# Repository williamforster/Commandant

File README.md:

SmartVac displays GPS and other data on a map.

# Usage

Download xampp or a similar software and find the website directory (htdocs)

Remove the default xampp webpage so the htdocs directory is empty.
Navigate to htdocs and clone into the current directory.

    git clone https://github.com/williamforster/SmartVac.git .

Download and install node.
Then install the project dependencies.

    npm install

Open your web browser and type 'localhost/phpmyadmin' in the address bar. Add a new database and run the sql in create_test_datatable.sql - or at least create a table with similar columns.

Add a user account in phpmyadmin and grant them Data priveleges.

Make a credentials.php file and enter the new fields. Credentials.php is in the .gitignore file so it won't be uploaded to the git repo.

    cp credentials_example.php credentials.php
    nano credentials.php

Build bundle.js with browserify. Bundles include only the js needed by the website.

    npm run build

Open localhost in your web browser

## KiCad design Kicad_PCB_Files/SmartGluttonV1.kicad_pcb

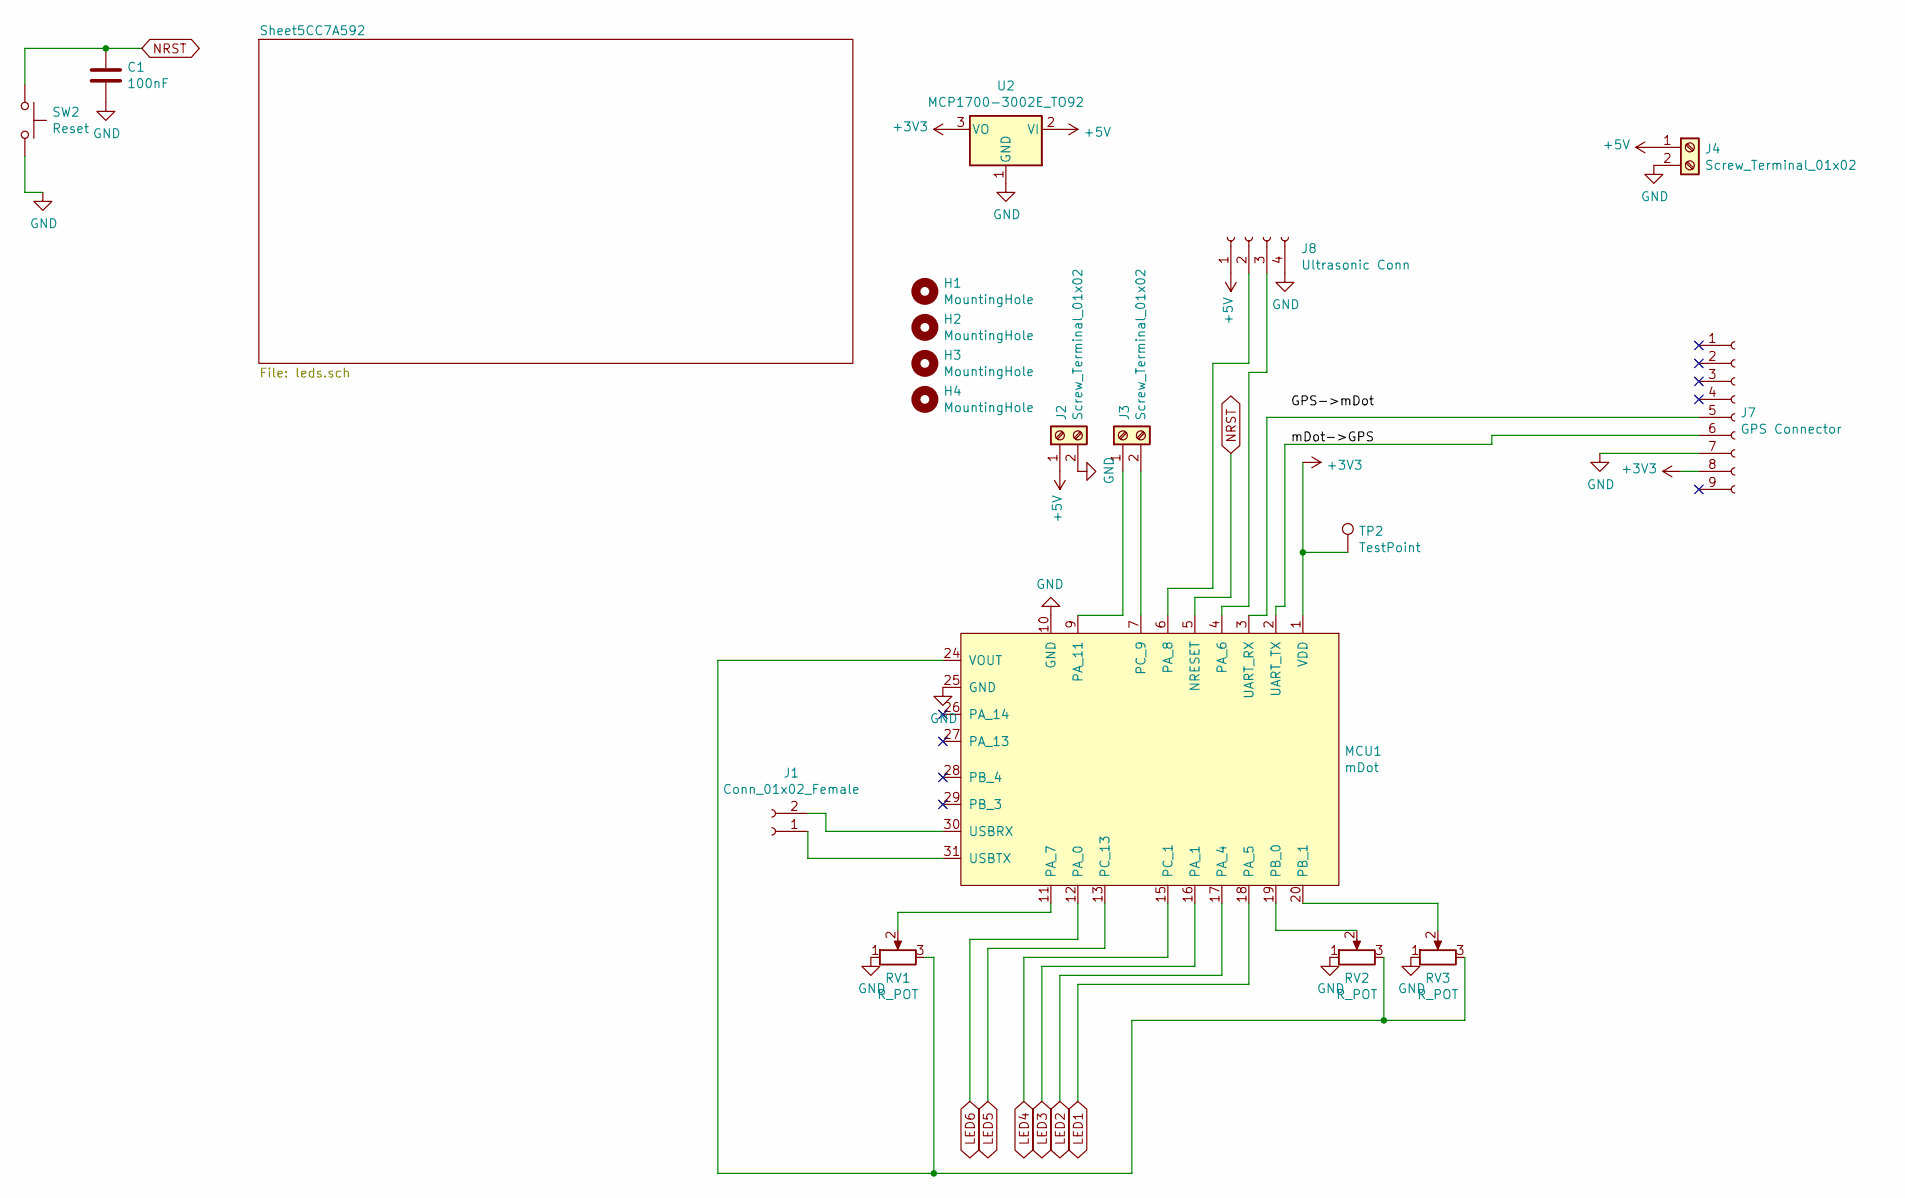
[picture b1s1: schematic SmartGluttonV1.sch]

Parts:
C1: 100nF; C_0805_2012Metric_Pad1.15x1.40mm_HandSolder
H1, H2, H3, H4: MountingHole; MountingHole_4mm
J1: Conn_01x02_Female; PinHeader_1x02_P2.54mm_Vertical
J2, J3, J4: Screw_Terminal_01x02; TerminalBlock_bornier-2_P5.08mm
J7: GPS Connector; Adafruit_GPS_Breakout
J8: Ultrasonic Conn; PinSocket_1x04_P2.54mm_Vertical
MCU1: mDot; mdot
RV1, RV2, RV3: R_POT; Potentiometer_Bourns_3296W_Vertical
SW2: Reset; SW_PUSH_6mm
TP2: TestPoint; TestPoint_Pad_3.0x3.0mm
U2: MCP1700-3002E_TO92; TO-92_HandSolder

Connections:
+3V3: J7.8, MCU1.1 (VDD), TP2.1, U2.3 (VO)
+5V: J2.1, J4.1, J8.1, U2.2 (VI); also elsewhere on the board
/mDot->GPS: J7.6, MCU1.2 (UART_TX)
GND: C1.2, J2.2, J4.2, J7.7, J8.4, MCU1.10 (GND), MCU1.25 (GND), RV1.1, RV2.1, RV3.1, SW2.2, U2.1 (GND); also elsewhere on the board
LED1: MCU1.18 (PA_5); also elsewhere on the board
LED2: MCU1.17 (PA_4); also elsewhere on the board
LED3: MCU1.16 (PA_1); also elsewhere on the board
LED4: MCU1.15 (PC_1); also elsewhere on the board
LED5: MCU1.13 (PC_13); also elsewhere on the board
LED6: MCU1.12 (PA_0); also elsewhere on the board
NRST: C1.1, MCU1.5 (NRESET), SW2.1
unnamed: J1.1, MCU1.31 (USBTX)
unnamed: J1.2, MCU1.30 (USBRX)
unnamed: J3.1, MCU1.9 (PA_11)
unnamed: J3.2, MCU1.7 (PC_9)
unnamed: J7.5, MCU1.3 (UART_RX)
unnamed: J8.2, MCU1.6 (PA_8)
unnamed: J8.3, MCU1.4 (PA_6)
unnamed: MCU1.11 (PA_7), RV1.2
unnamed: MCU1.19 (PB_0), RV2.2
unnamed: MCU1.20 (PB_1), RV3.2
unnamed: MCU1.24 (VOUT), RV1.3, RV2.3, RV3.3

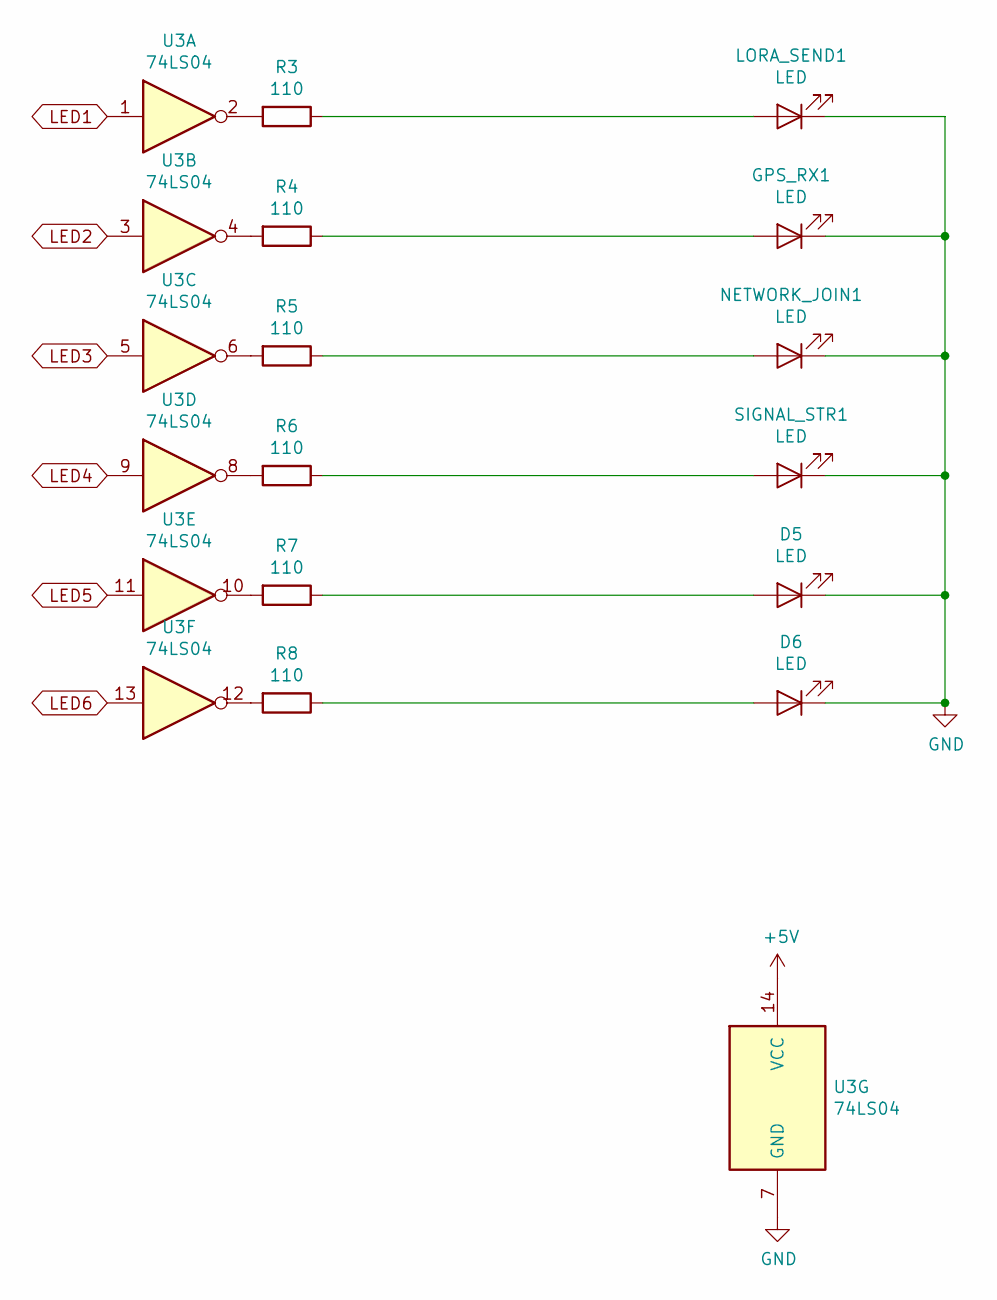
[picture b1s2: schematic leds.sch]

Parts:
D5, D6: LED; LED_D3.0mm
GPS_RX1: LED; LED_D3.0mm
LORA_SEND1: LED; LED_D3.0mm
NETWORK_JOIN1: LED; LED_D3.0mm
R3, R4, R5, R6, R7, R8: 110; R_0805_2012Metric_Pad1.15x1.40mm_HandSolder
SIGNAL_STR1: LED; LED_D3.0mm
U3: 74LS04; DIP-14_W7.62mm_LongPads

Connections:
+5V: U3.14 (VCC); also elsewhere on the board
GND: D5.1 (K), D6.1 (K), GPS_RX1.1 (K), LORA_SEND1.1 (K), NETWORK_JOIN1.1 (K), SIGNAL_STR1.1 (K), U3.7 (GND); also elsewhere on the board
LED1: U3.1; also elsewhere on the board
LED2: U3.3; also elsewhere on the board
LED3: U3.5; also elsewhere on the board
LED4: U3.9; also elsewhere on the board
LED5: U3.11; also elsewhere on the board
LED6: U3.13; also elsewhere on the board
unnamed: D5.2 (A), R7.1
unnamed: D6.2 (A), R8.1
unnamed: GPS_RX1.2 (A), R4.1
unnamed: LORA_SEND1.2 (A), R3.1
unnamed: NETWORK_JOIN1.2 (A), R5.1
unnamed: R3.2, U3.2
unnamed: R4.2, U3.4
unnamed: R5.2, U3.6
unnamed: R6.1, SIGNAL_STR1.2 (A)
unnamed: R6.2, U3.8
unnamed: R7.2, U3.10
unnamed: R8.2, U3.12

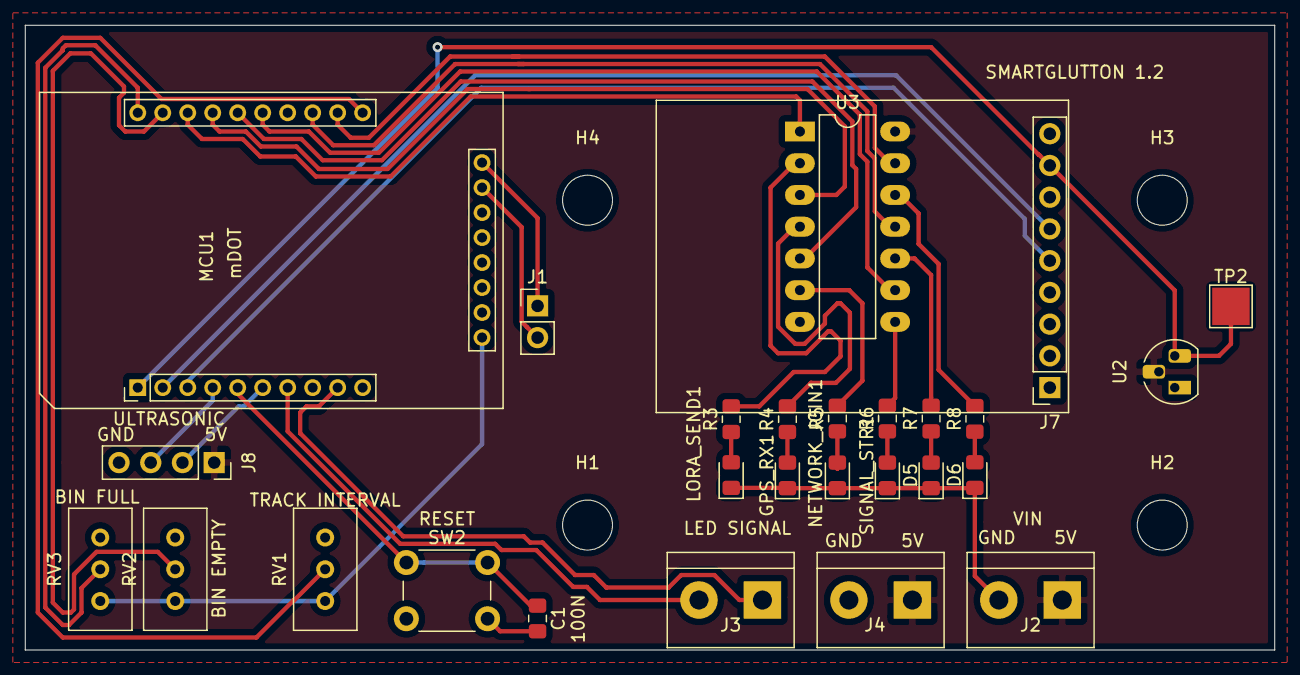
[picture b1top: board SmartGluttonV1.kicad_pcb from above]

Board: 2 copper layers, 100.0 x 50.0 mm, 31 parts (0 on the bottom side), 34 nets.

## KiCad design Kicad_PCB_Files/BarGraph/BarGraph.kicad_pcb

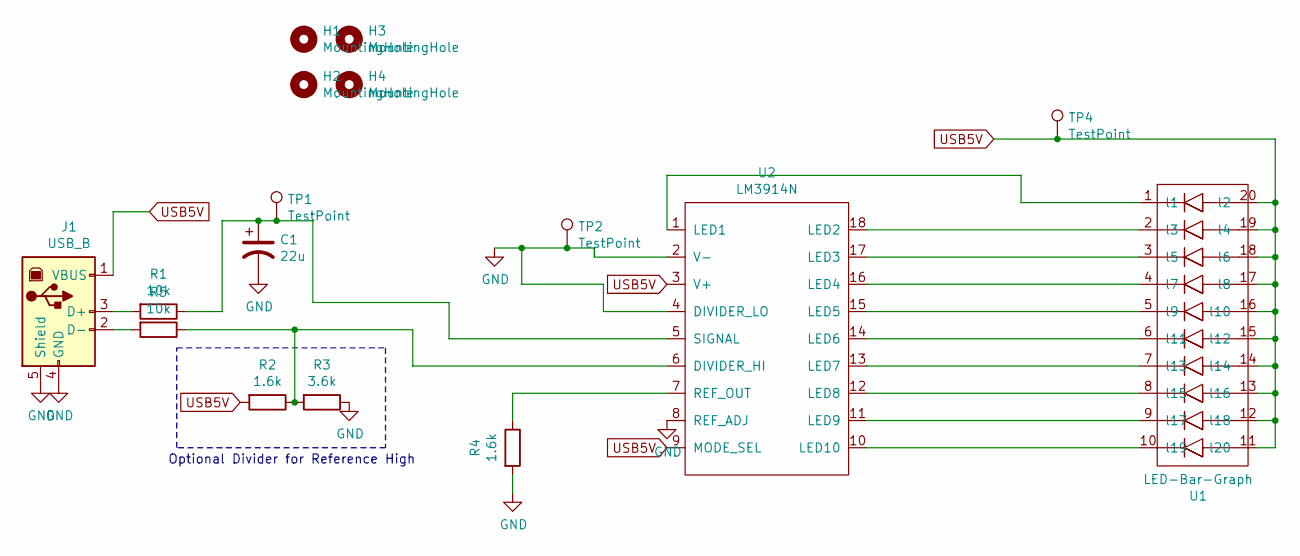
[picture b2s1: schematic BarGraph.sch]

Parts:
C1: 22u; CP_Radial_D5.0mm_P2.50mm
H1, H2, H3, H4: MountingHole; MountingHole_4mm
J1: USB_B; USB_B_Molex_USB-67068-xx1x_StraightTab_Horizontal
R1, R5: 10k; R_Axial_DIN0207_L6.3mm_D2.5mm_P10.16mm_Horizontal
R2: 1.6k; R_Axial_DIN0207_L6.3mm_D2.5mm_P2.54mm_Vertical
R3: 3.6k; R_Axial_DIN0207_L6.3mm_D2.5mm_P2.54mm_Vertical
R4: 1.6k; R_Axial_DIN0207_L6.3mm_D2.5mm_P10.16mm_Horizontal
TP1, TP2, TP4: TestPoint; TestPoint_Pad_2.5x2.5mm
U1: LED-Bar-Graph; led-bar-graph-10
U2: LM3914N; DIP-18_W7.62mm_Socket_LongPads

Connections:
GND: C1.2, J1.4 (GND), J1.5 (Shield), R3.1, R4.2, TP2.1, U2.2 (V-), U2.4 (DIVIDER_LO), U2.8 (REF_ADJ)
unnamed: C1.1, R1.1, TP1.1, U2.5 (SIGNAL)
unnamed: J1.2 (D-), R5.2
unnamed: J1.3 (D+), R1.2
unnamed: R2.1, R3.2, R5.1, U2.6 (DIVIDER_HI)
unnamed: R4.1, U2.7 (REF_OUT)
unnamed: U1.1 (l1), U2.1 (LED1)
unnamed: U1.2 (l3), U2.18 (LED2)
unnamed: U1.3 (l5), U2.17 (LED3)
unnamed: U1.4 (l7), U2.16 (LED4)
unnamed: U1.5 (l9), U2.15 (LED5)
unnamed: U1.6 (l11), U2.14 (LED6)
unnamed: U1.7 (l13), U2.13 (LED7)
unnamed: U1.8 (l15), U2.12 (LED8)
unnamed: U1.9 (l17), U2.11 (LED9)
unnamed: U1.10 (l19), U2.10 (LED10)
USB5V: J1.1 (VBUS), R2.2, TP4.1, U1.11 (l20), U1.12 (l18), U1.13 (l16), U1.14 (l14), U1.15 (l12), U1.16 (l10), U1.17 (l8), U1.18 (l6), U1.19 (l4), U1.20 (l2), U2.3 (V+), U2.9 (MODE_SEL)

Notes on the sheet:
Optional Divider for Reference High

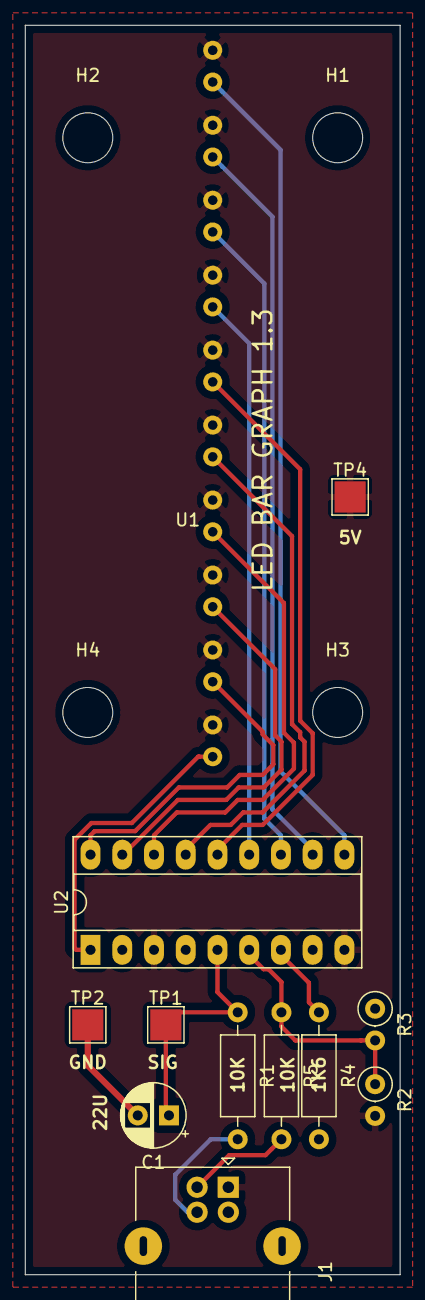
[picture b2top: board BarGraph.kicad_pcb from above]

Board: 2 copper layers, 30.0 x 100.0 mm, 16 parts (0 on the bottom side), 17 nets.

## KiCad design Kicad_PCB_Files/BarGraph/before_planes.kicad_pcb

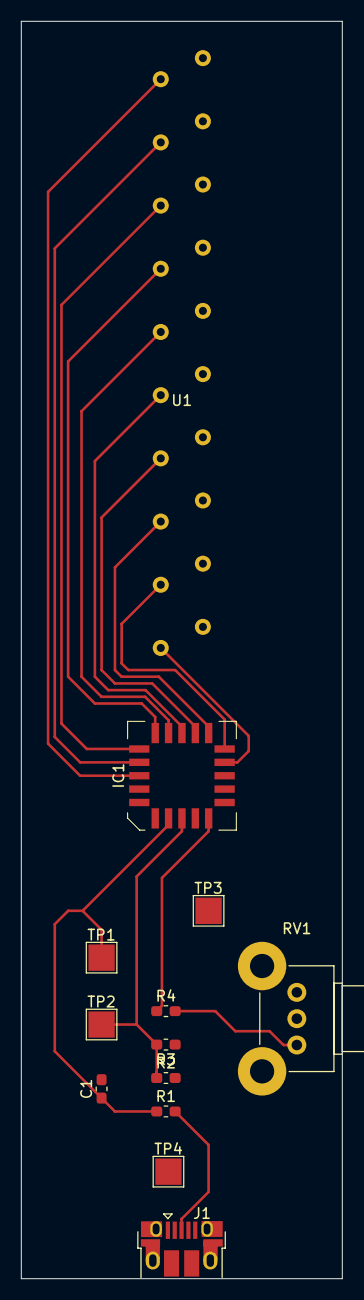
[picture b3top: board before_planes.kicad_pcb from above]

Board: 2 copper layers, 30.5 x 119.4 mm, 13 parts (0 on the bottom side), 17 nets.

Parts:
C1: 22u; C_0603_1608Metric_Pad1.05x0.95mm_HandSolder
IC1: LM3914VX_NOPB; PLCC-20
J1: USB_B_Micro; USB_Micro-B_Amphenol_10103594-0001LF_Horizontal
R1, R2: 10k; R_0603_1608Metric_Pad1.05x0.95mm_HandSolder
R3: 16k; R_0603_1608Metric_Pad1.05x0.95mm_HandSolder
R4: 1.6k; R_0603_1608Metric_Pad1.05x0.95mm_HandSolder
RV1: R_POT; Potentiometer_Alps_RK09K_Single_Horizontal
TP1, TP2, TP3, TP4: TestPoint; TestPoint_Pad_2.5x2.5mm
U1: LED-Bar-Graph; led-bar-graph-10

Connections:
GND: C1.2, IC1.2, IC1.4, IC1.10, J1.5, J1.6, R3.1, RV1.2, TP3.1
unnamed: C1.1, IC1.5, R1.1, TP1.1
unnamed: IC1.1, U1.1
unnamed: IC1.6, R2.1, R3.2, TP2.1
unnamed: IC1.8, R4.1
unnamed: IC1.12, U1.10
unnamed: IC1.13, U1.9
unnamed: IC1.14, U1.8
unnamed: IC1.15, U1.7
unnamed: IC1.16, U1.6
unnamed: IC1.17, U1.5
unnamed: IC1.18, U1.4
unnamed: IC1.19, U1.3
unnamed: IC1.20, U1.2
unnamed: J1.3, R1.2
unnamed: R4.2, RV1.1
USB5V: IC1.3, IC1.11, J1.1, R2.2, TP4.1, U1.11, U1.12, U1.13, U1.14, U1.15, U1.16, U1.17, U1.18, U1.19, U1.20

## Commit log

2019-03-21 Changed the map, added js and style directories
    partway through implementing ajax data retrieval
2019-03-21 php script now returns data in geojson format, js file adds it to the view as a vector layer
2019-03-21 Display popup when mouseover point
2019-03-21 add a screenshot and make the popup look nicer
2019-03-21 add image to readme
2019-03-21 scale down screenshot
2019-03-22 Formatting & stuff
2019-03-22 Change to doing geojson manipulation on client side - will reduce num. queries eventually.
2019-03-22 Change the displayed dtime format
2019-04-04 Updates to database table structure
2019-04-19 Data sorted by days now
2019-04-20 All sorts of good stuff. Refactored for better project structure. Map pans to displayed data, displayed data renders during animation, colors are better.
2019-04-23 Added showing time difference between two selected points
2019-04-24 Add indicator for selected path. Make popup translucent and remove popup close button.
2019-04-24 Fixed flickering UI elements. Added more robustness if the database errors. Moved main.js to js folder.
2019-04-26 Changed code style of imports and graphics style
2019-05-08 Fix sorting function on google chrome browsers
2019-07-24 Make map big
2019-07-25 Change styles and add logout button
2019-07-25 Add context menu. Still needs delete function to be implemented
2019-07-28 Add qunit testing with localhost:8080/test.html
2019-07-28 Hoverselect stops being active while right click menu open
2019-07-29 Deleting data mostly done
2019-07-29 update datatable structure
2019-08-10 allow for snr value + add most recent location icon
2019-08-14 Add a checkbox to show/hide gps tracking layers
2019-08-14 Remove unnecessary imports
2019-08-18 Add rssi and snr to datapoint popup
2019-08-23 Slider partially done
2019-08-23 implemented rangeslider somewhat
2019-08-23 Pan to data on refresh, change track color
2019-08-24 Add auth check to all files (need to check group still)
2019-08-24 Add logout function
2019-08-25 Rangeslider doubles timespan when set to absolute minimum
2019-08-26 Most recent data shown on top
2019-09-27 Add hdop slider
2019-10-10 Add hdop to readout & change hdop default
2019-10-24 remove logout button
